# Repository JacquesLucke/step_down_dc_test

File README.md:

[Schematic](https://jacqueslucke.github.io/step_down_dc_test/step_down_dc_test_schematic.pdf)

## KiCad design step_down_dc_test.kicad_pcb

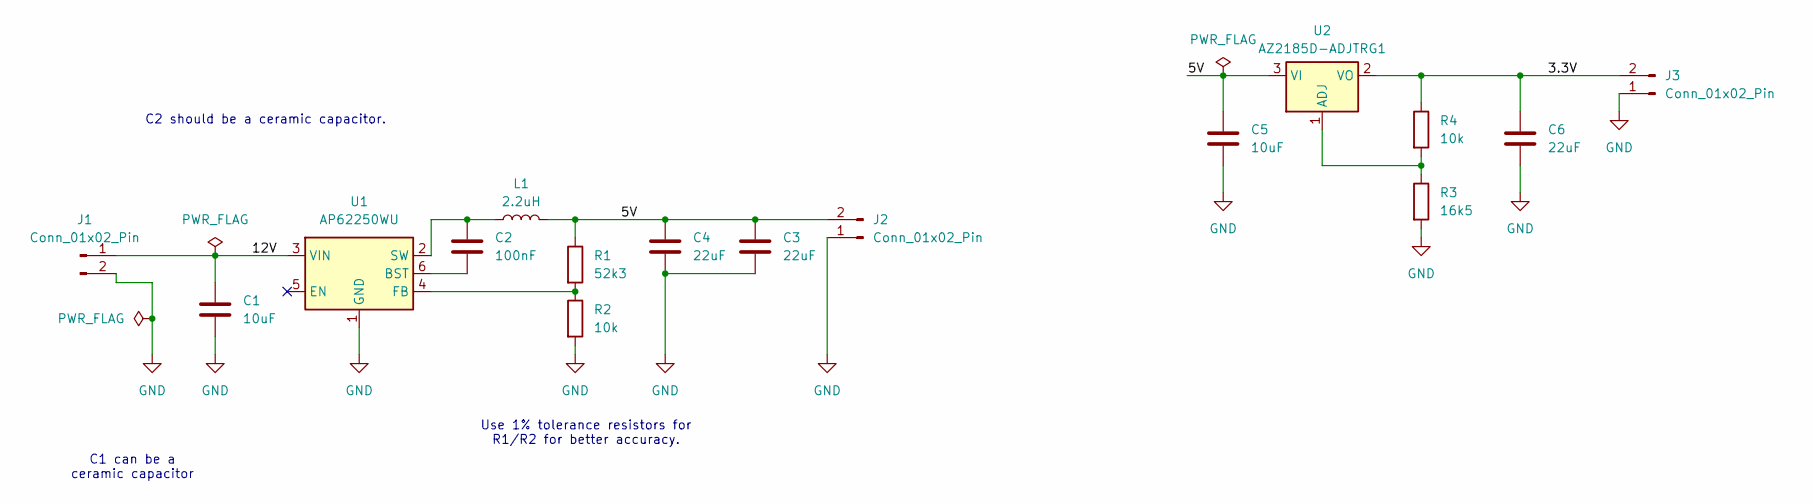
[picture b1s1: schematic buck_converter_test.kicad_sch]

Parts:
C1, C5: 10uF; C_0603_1608Metric_Pad1.08x0.95mm_HandSolder
C2: 100nF; C_0603_1608Metric_Pad1.08x0.95mm_HandSolder
C3, C4, C6: 22uF; C_0603_1608Metric_Pad1.08x0.95mm_HandSolder
J1, J2, J3: Conn_01x02_Pin; PinHeader_1x02_P2.54mm_Vertical_SMD_Pin1Left
L1: 2.2uH; L_1210_3225Metric_Pad1.42x2.65mm_HandSolder
R1: 52k3; R_0603_1608Metric_Pad0.98x0.95mm_HandSolder
R2, R4: 10k; R_0603_1608Metric_Pad0.98x0.95mm_HandSolder
R3: 16k5; R_0603_1608Metric_Pad0.98x0.95mm_HandSolder
U1: AP62250WU; TSOT-23-6
U2: AZ2185D-ADJTRG1; TO-252-2

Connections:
/3.3V: C6.1, J3.2, R4.1, U2.2 (VO)
/5V: C3.1, C4.1, C5.1, J2.2, L1.2, R1.1, U2.3 (VI)
/12V: C1.1, J1.1, U1.3 (VIN)
GND: C1.2, C3.2, C4.2, C5.2, C6.2, J1.2, J2.1, J3.1, R2.2, R3.2, U1.1 (GND)
unnamed: C2.2, U1.6 (BST)
unnamed: R1.2, R2.1, U1.4 (FB)
unnamed: C2.1, L1.1, U1.2 (SW)
unnamed: R3.1, R4.2, U2.1 (ADJ)

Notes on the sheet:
C1 can be a ceramic capacitor
C2 should be a ceramic capacitor.
Use 1% tolerance resistors for R1/R2 for better accuracy.

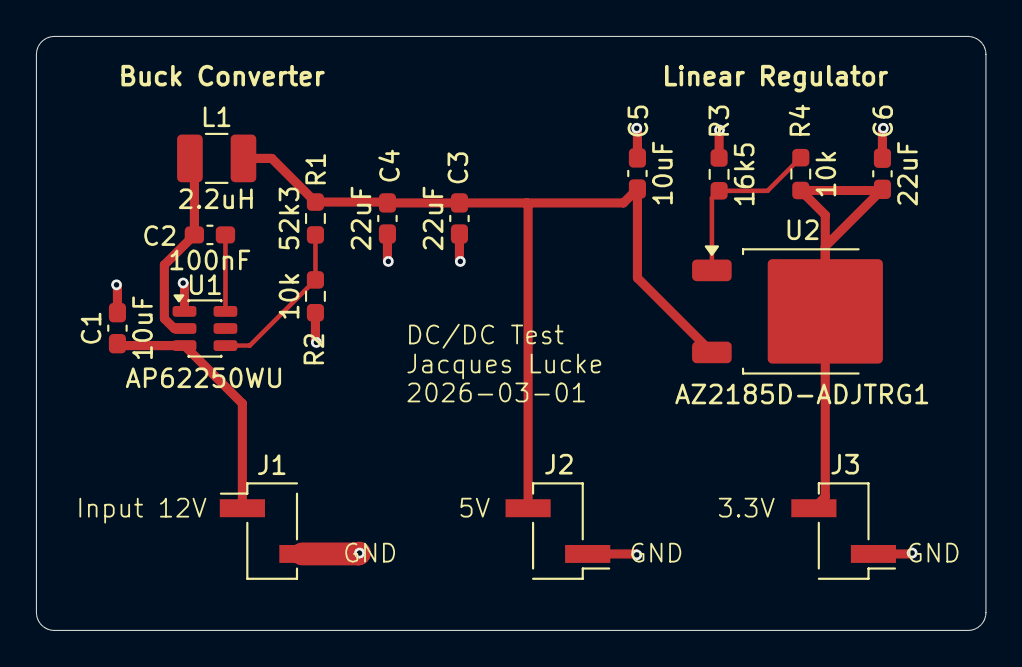
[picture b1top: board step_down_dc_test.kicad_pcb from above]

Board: 2 copper layers, 52.8 x 33.0 mm, 16 parts (0 on the bottom side), 8 nets.

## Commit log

2026-03-01 rename
2026-03-01 progress
2026-03-01 try kibot
2026-03-01 try setting kicad version
2026-03-01 potential fix
2026-03-01 try schematic
2026-03-01 try putting files in output dir
2026-03-01 cleanup
2026-03-01 try render 3D
2026-03-01 test blender render
2026-03-01 test
2026-03-01 typo
2026-03-01 render
2026-03-01 fix link
